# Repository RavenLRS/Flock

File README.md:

Flock
=====

Flock is an inter-vehicle peer to peer communication protocol
for data exchange between remote controlled and/or autonomous vehicles.

The core protocol supports some basic data exchange, but also
allows host to broadcast arbitrary data. This 

## Interesting stuff

- [FlockOne](hardware/FlockOne): STM32F0, low cost flock board
- [Firmware](firmware)
- [Protocol Specification](docs)

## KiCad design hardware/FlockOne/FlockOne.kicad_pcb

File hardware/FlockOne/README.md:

FlockOne
========

This is a cheap STM32F0 based board with a total DIY cost
around $4 per board. Users with previous soldering experience
should have no problem building it with just a soldering iron.

If you have never soldered SMD components, don't be afraid! All
the components but the LoRa module are very cheap, so this design
is also a good project to get you started with SMD. Just make sure
to use a fine tip, tweezers and copious amounts of flux.

### BOM

- 1x [STM32F030F4P6][1] (10pcs, \~$0.35/pc)
- 1x [Ai-Thinker Ra-02][2] (1pc, \~$2.65/pc)
- 1x [100 nF 0603 Capacitor][3] (**\***) (100pcs, $0.01/pc)
- 2x [4.7 uF 0603 Capacitor][3] (**\***) (100pcs, $0.01/pc)
- 2x [10 kOhm 0603 Resistor][4] (**\***) (100pcs, $0.01/pc)
- 1x [330 Ohm 0603 Resistor][4] (**\***) (100pcs, $0.01/pc)
- 1x [MIC5219-3.3BM5][5] (10pcs, $0.09/pc)
- 1x [0603 LED][6] (**\***) (100pcs, $0.01/pc)

(**\***) Listing with multiple values, select the right one!

### PCB

Use the [FlockOne.zip][FlockOne.zip] file to order the PCB from your
fabrication service of choice. Some popular manufacturers for
hobbyists:

- JLCPCB: ~$7 for 10 boards + shipping (\~$0.70/pc)
- OshPark: ~$2.85 for 3 bords + shipping (\~$0.95/pc)

### Antenna

Any 433Mhz properly tuned antenna should work, there's no reason
to use a high gain one. The RA-02 module includes an IPEX 
connector, so if you plan to use an antenna with a different 
connector (e.g. SMA) you should buy a pigtail too. Make sure to 
pick an ommnidirectional one. These are some examples:

- [433MHz Spring Antenna][ant1] (1pc, \~$0.58/pc)

[1]: http://s.click.aliexpress.com/e/bBTYCsGo
[2]: http://s.click.aliexpress.com/e/YACp66M
[3]: http://s.click.aliexpress.com/e/ljKo0PW
[4]: http://s.click.aliexpress.com/e/jFzlBWo
[5]: http://s.click.aliexpress.com/e/bK4Lefbi
[6]: http://s.click.aliexpress.com/e/bfQQhzdW
[FlockOne.zip]: gerbers/FlockOne.zip
[ant1]: https://www.aliexpress.com/item/433MHz-spring-antenna-3dBi-wireless-module-digital-transmit-antenna-IPEX-U-FL-interface-for-Rola-Module/32904294792.html

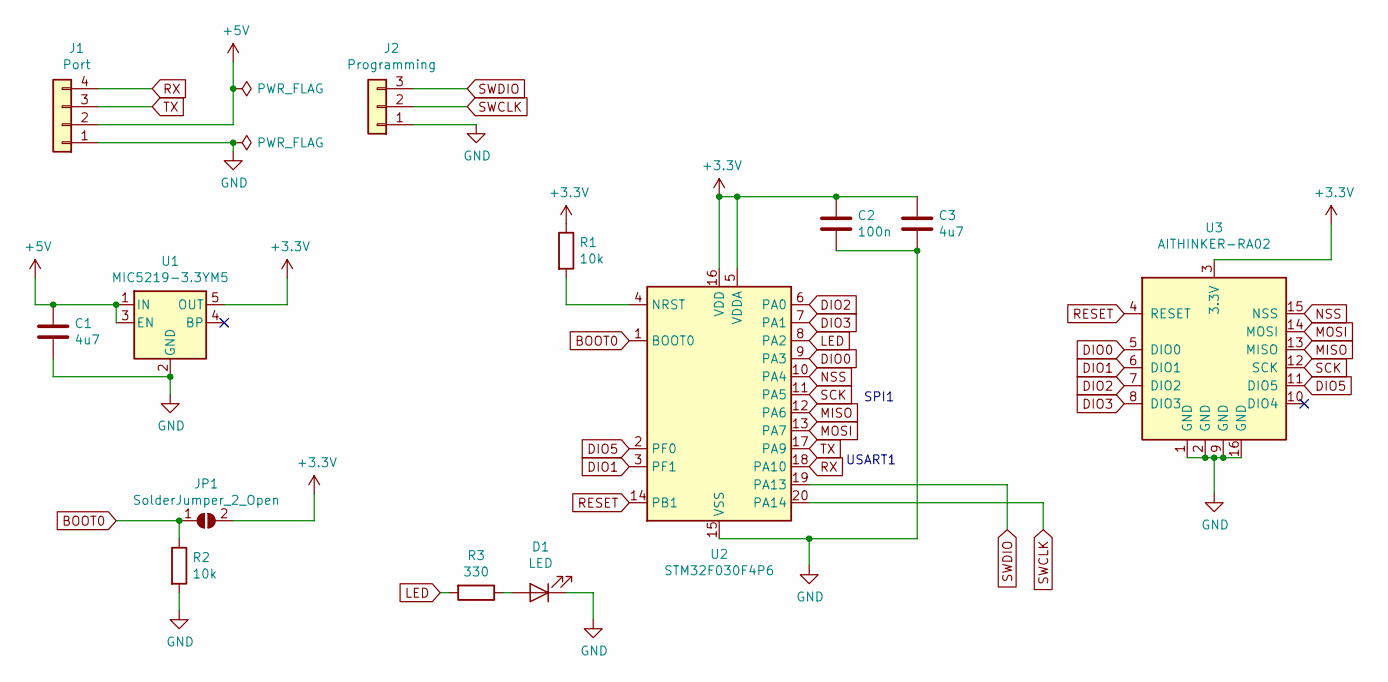
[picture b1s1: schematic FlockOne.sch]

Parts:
C1, C3: 4u7; C_0603_1608Metric_Pad1.05x0.95mm_HandSolder
C2: 100n; C_0603_1608Metric_Pad1.05x0.95mm_HandSolder
D1: LED; LED_0603_1608Metric_Pad1.05x0.95mm_HandSolder
J1: Port; PinHeader_1x04_P2.54mm_Vertical
J2: Programming; PinHeader_1x03_P1.27mm_Vertical
JP1: SolderJumper_2_Open; SolderJumper-2_P1.3mm_Open_RoundedPad1.0x1.5mm
R1, R2: 10k; R_0603_1608Metric_Pad1.05x0.95mm_HandSolder
R3: 330; R_0603_1608Metric_Pad1.05x0.95mm_HandSolder
U1: MIC5219-3.3YM5; SOT-23-5
U2: STM32F030F4P6; TSSOP-20_4.4x6.5mm_P0.65mm
U3: AITHINKER-RA02; AITHINKER_RA02

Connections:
+3V3: C2.1, C3.1, JP1.2 (B), R1.1, U1.5 (OUT), U2.5 (VDDA), U2.16 (VDD), U3.3 (3.3V)
+5V: C1.1, J1.2, U1.1 (IN), U1.3 (EN)
BOOT0: JP1.1 (A), R2.1, U2.1 (BOOT0)
DIO0: U2.9 (PA3), U3.5 (DIO0)
DIO1: U2.3 (PF1), U3.6 (DIO1)
DIO2: U2.6 (PA0), U3.7 (DIO2)
DIO3: U2.7 (PA1), U3.8 (DIO3)
DIO5: U2.2 (PF0), U3.11 (DIO5)
GND: C1.2, C2.2, C3.2, D1.1 (K), J1.1, J2.1, R2.2, U1.2 (GND), U2.15 (VSS), U3.1 (GND), U3.2 (GND), U3.9 (GND), U3.16 (GND)
LED: R3.2, U2.8 (PA2)
MISO: U2.12 (PA6), U3.13 (MISO)
MOSI: U2.13 (PA7), U3.14 (MOSI)
NSS: U2.10 (PA4), U3.15 (NSS)
unnamed: D1.2 (A), R3.1
unnamed: R1.2, U2.4 (NRST)
RESET: U2.14 (PB1), U3.4 (RESET)
RX: J1.4, U2.18 (PA10)
SCK: U2.11 (PA5), U3.12 (SCK)
SWCLK: J2.2, U2.20 (PA14)
SWDIO: J2.3, U2.19 (PA13)
TX: J1.3, U2.17 (PA9)

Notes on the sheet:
SPI1
USART1

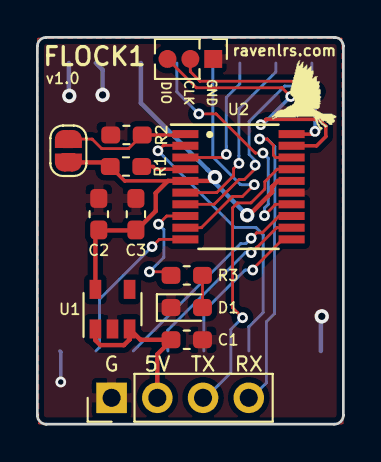
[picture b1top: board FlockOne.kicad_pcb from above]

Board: 2 copper layers, 17.0 x 21.5 mm, 13 parts (1 on the bottom side), 21 nets.

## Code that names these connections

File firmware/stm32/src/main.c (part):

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
    LL_AHB1_GRP1_EnableClock(LL_AHB1_GRP1_PERIPH_GPIOA);
    /**SPI1 GPIO Configuration  
  PA5   ------> SPI1_SCK
  PA6   ------> SPI1_MISO
  PA7   ------> SPI1_MOSI 
  PA4   ------> SPI1_NSS (software)
  */
    GPIO_InitStruct.Pin = LL_GPIO_PIN_5;
    GPIO_InitStruct.Mode = LL_GPIO_MODE_ALTERNATE;
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
    LL_AHB1_GRP1_EnableClock(LL_AHB1_GRP1_PERIPH_GPIOA);
    /**USART1 GPIO Configuration  
  PA9   ------> USART1_TX
  PA10   ------> USART1_RX 
  */
    GPIO_InitStruct.Pin = LL_GPIO_PIN_9;
    GPIO_InitStruct.Mode = LL_GPIO_MODE_ALTERNATE;
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
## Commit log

2019-04-06 Initial commit for FLOCK
2019-04-06 Fix some MD formatting errors
2019-04-09 Fix missing connection to the EN pin on MIC5219
2019-04-09 Fix formatting
2019-04-09 Fix links to antenna and gerbers file
2019-04-11 Move DIO5 to HSE bypass input
    This lets use use the xtal in the LoRa module as HSE rather than
    using it for trimming HSI.
2019-04-11 Split protocol definition from SERIAL transport
2019-04-12 Add command for exchanging host information
    Also, reword the spec to refer to each node in a flock as bird.
2019-04-12 Add spec for MSP transport
2019-04-13 Define heading as a quantization
    This way we don't have to deal with units in its definition
2019-04-13 Add libflock
    A portable C library for both host and device side implementations.
    Still incomplete (only quantization functions are implemented).
2019-04-14 Add error reporting to flock_radio_current_freq
2019-04-14 Initial implementation for the FlockOne firmware
2019-04-15 Uncomment flock quantization functions
    There's no need to manually disable them when LTO is enabled
2019-04-15 Enable lrintf() even with SOFTFP
    If needed, a size optimized 3rd party library can be used to
    reduce flash usage
2019-04-15 Initialize PRNG on startup from SX127x's
    Use RSSI Wideband as a source of randomness
2019-04-15 Add struct definitions for the flock air protocol

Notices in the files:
firmware/stm32/src/main.c:
(C) COPYRIGHT STMicroelectronics *****END OF FILE
